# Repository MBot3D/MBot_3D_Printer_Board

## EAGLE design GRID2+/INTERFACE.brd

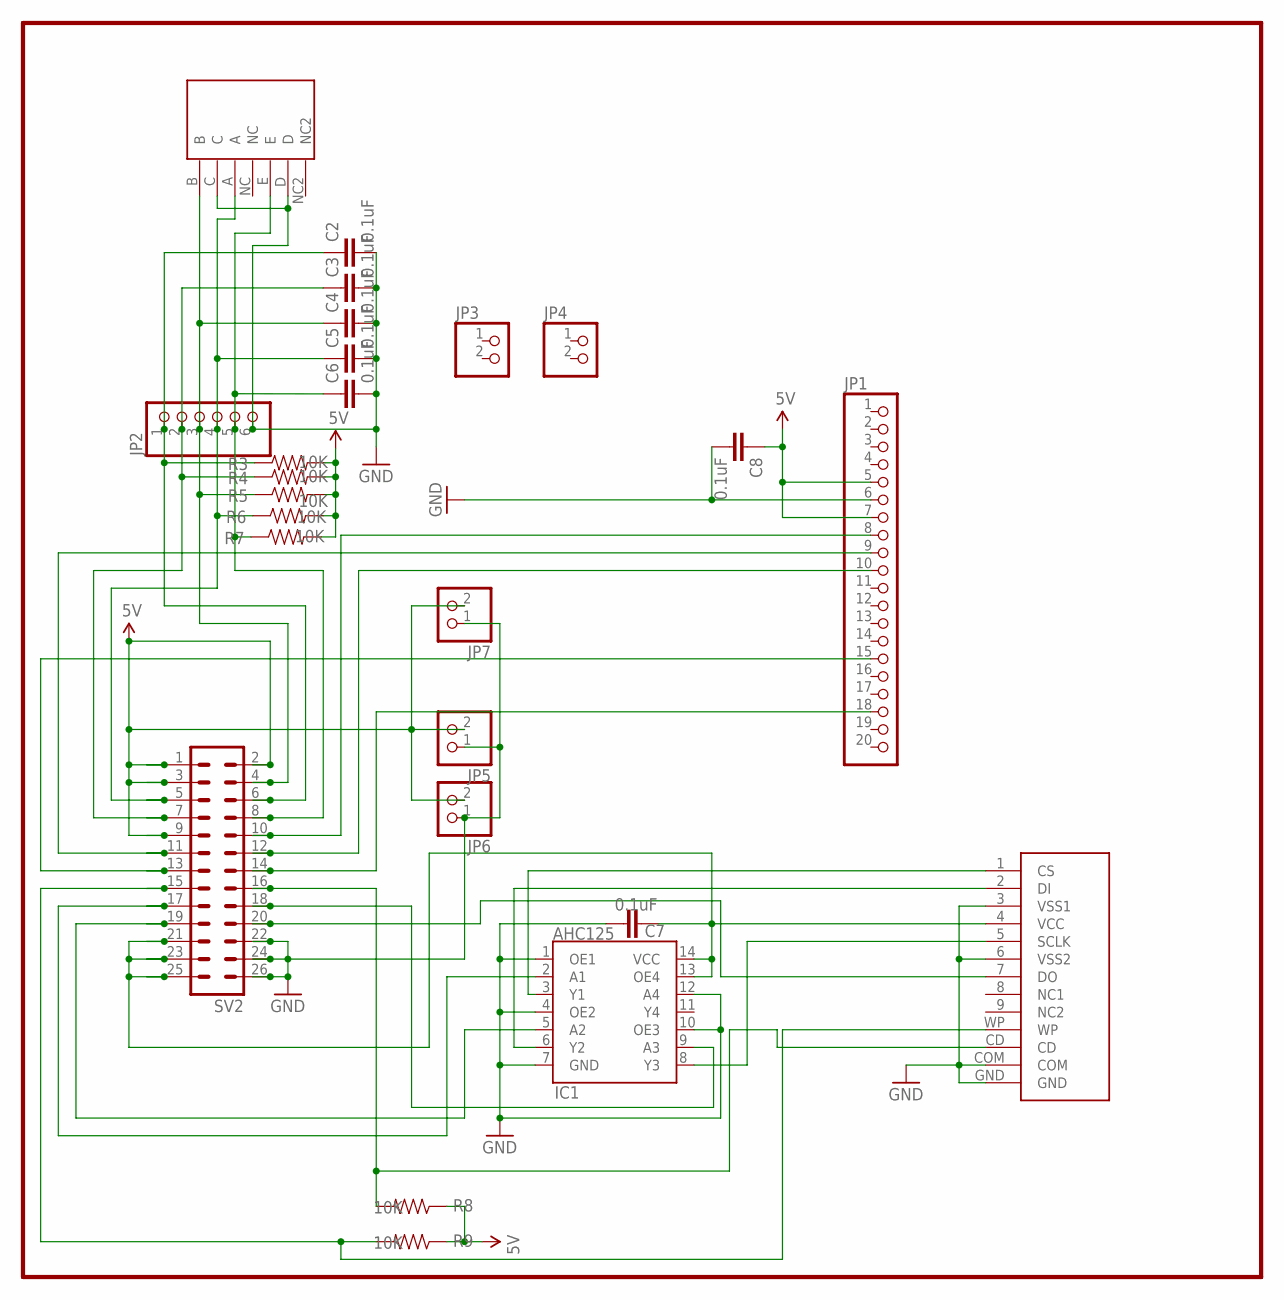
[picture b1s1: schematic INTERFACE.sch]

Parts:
C2, C3, C4, C5, C6, C7, C8: 0.1uF; 0805
IC1: AHC125; DIN14
JP1: PINHD-1X20; 1X20
JP2: PINHD-1X6; 1X06
JP3, JP4, JP5, JP6, JP7: PINHD-1X2; 1X02
Q2: SDCARD
R3, R4, R5, R6, R7, R8, R9: 10K; 0805
S2: DJFS; PIN5
SV2: ML26L

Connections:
5V: C8.1, JP1.5, JP1.7, JP5.2, JP6.2, JP7.2, R3.2, R4.2, R5.2, R6.2, R7.2, R8.1, R9.1, SV2.1, SV2.2, SV2.3, SV2.9
GND2: C2.2, C3.2, C4.2, C5.2, C6.2, C7.2, C8.2, IC1.1 (OE1), IC1.4 (OE2), IC1.7 (GND), IC1.10 (OE3), IC1.12 (A4), JP1.6, JP2.6, JP5.1, JP6.1, JP7.1, Q2.3 (VSS1), Q2.6 (VSS2), Q2.COM, Q2.GND, S2.C, S2.D, SV2.22, SV2.24, SV2.26
unnamed: IC1.3 (Y1), Q2.1 (CS)
unnamed: C2.1, JP2.1, R3.1, SV2.6
unnamed: IC1.2 (A1), SV2.17
unnamed: IC1.6 (Y2), Q2.2 (DI)
unnamed: Q2.CD, R8.2, SV2.16
unnamed: Q2.7 (DO), SV2.20
unnamed: JP1.15, SV2.13
unnamed: JP1.8, SV2.10
unnamed: JP1.10, SV2.12
unnamed: JP1.9, SV2.11
unnamed: JP1.18, SV2.14
unnamed: IC1.8 (Y3), Q2.5 (SCLK)
unnamed: C3.1, JP2.2, R4.1, SV2.7
unnamed: C4.1, JP2.3, R5.1, S2.B, SV2.4
unnamed: C5.1, JP2.4, R6.1, S2.A, SV2.5
unnamed: C6.1, JP2.5, R7.1, S2.E, SV2.8
unnamed: Q2.WP, R9.2, SV2.15
unnamed: IC1.5 (A2), SV2.19
unnamed: C7.1, IC1.13 (OE4), IC1.14 (VCC), Q2.4 (VCC), SV2.21, SV2.23, SV2.25
unnamed: IC1.9 (A3), SV2.18

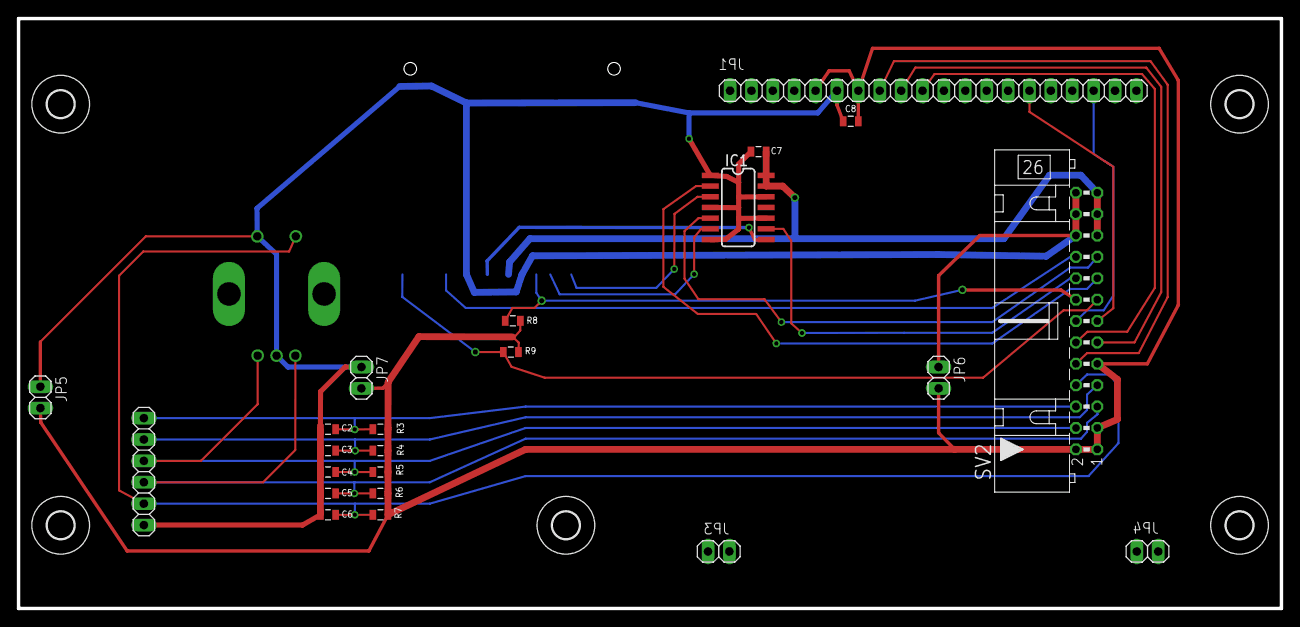
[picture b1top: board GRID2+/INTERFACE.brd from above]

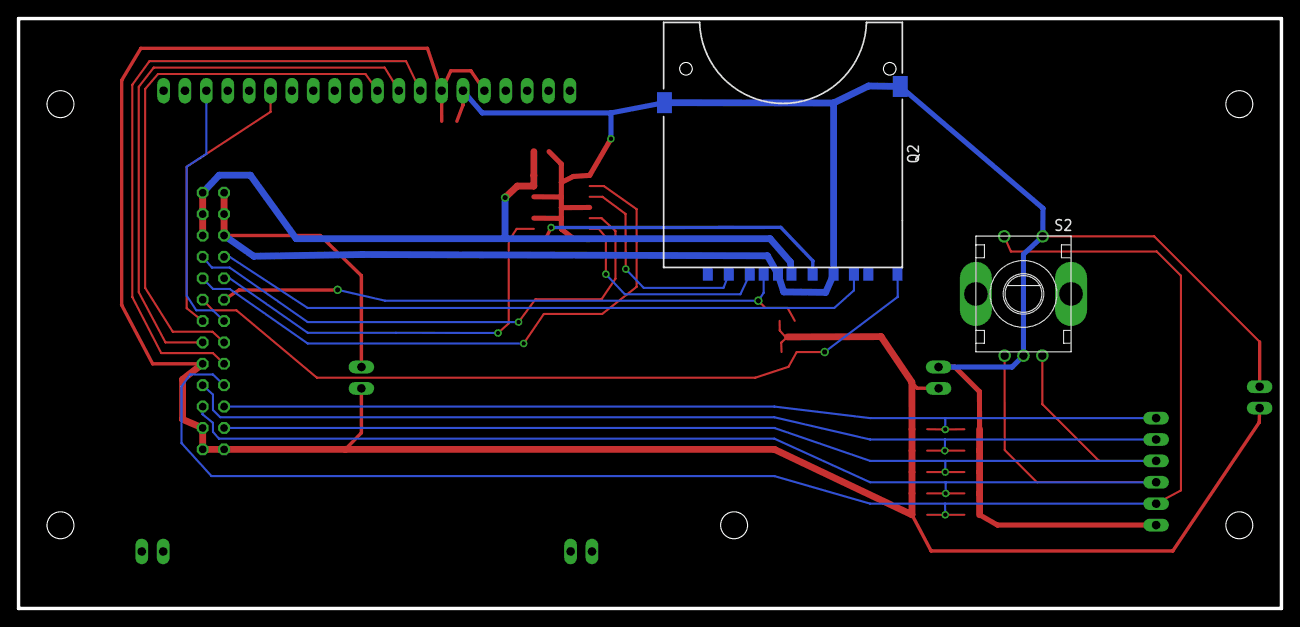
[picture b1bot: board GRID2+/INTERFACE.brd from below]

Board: 2 copper layers, 150.0 x 70.1 mm, 30 parts (2 on the bottom side), 22 nets.

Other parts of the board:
U$3, U$5, U$11, U$12, U$13: 3,2

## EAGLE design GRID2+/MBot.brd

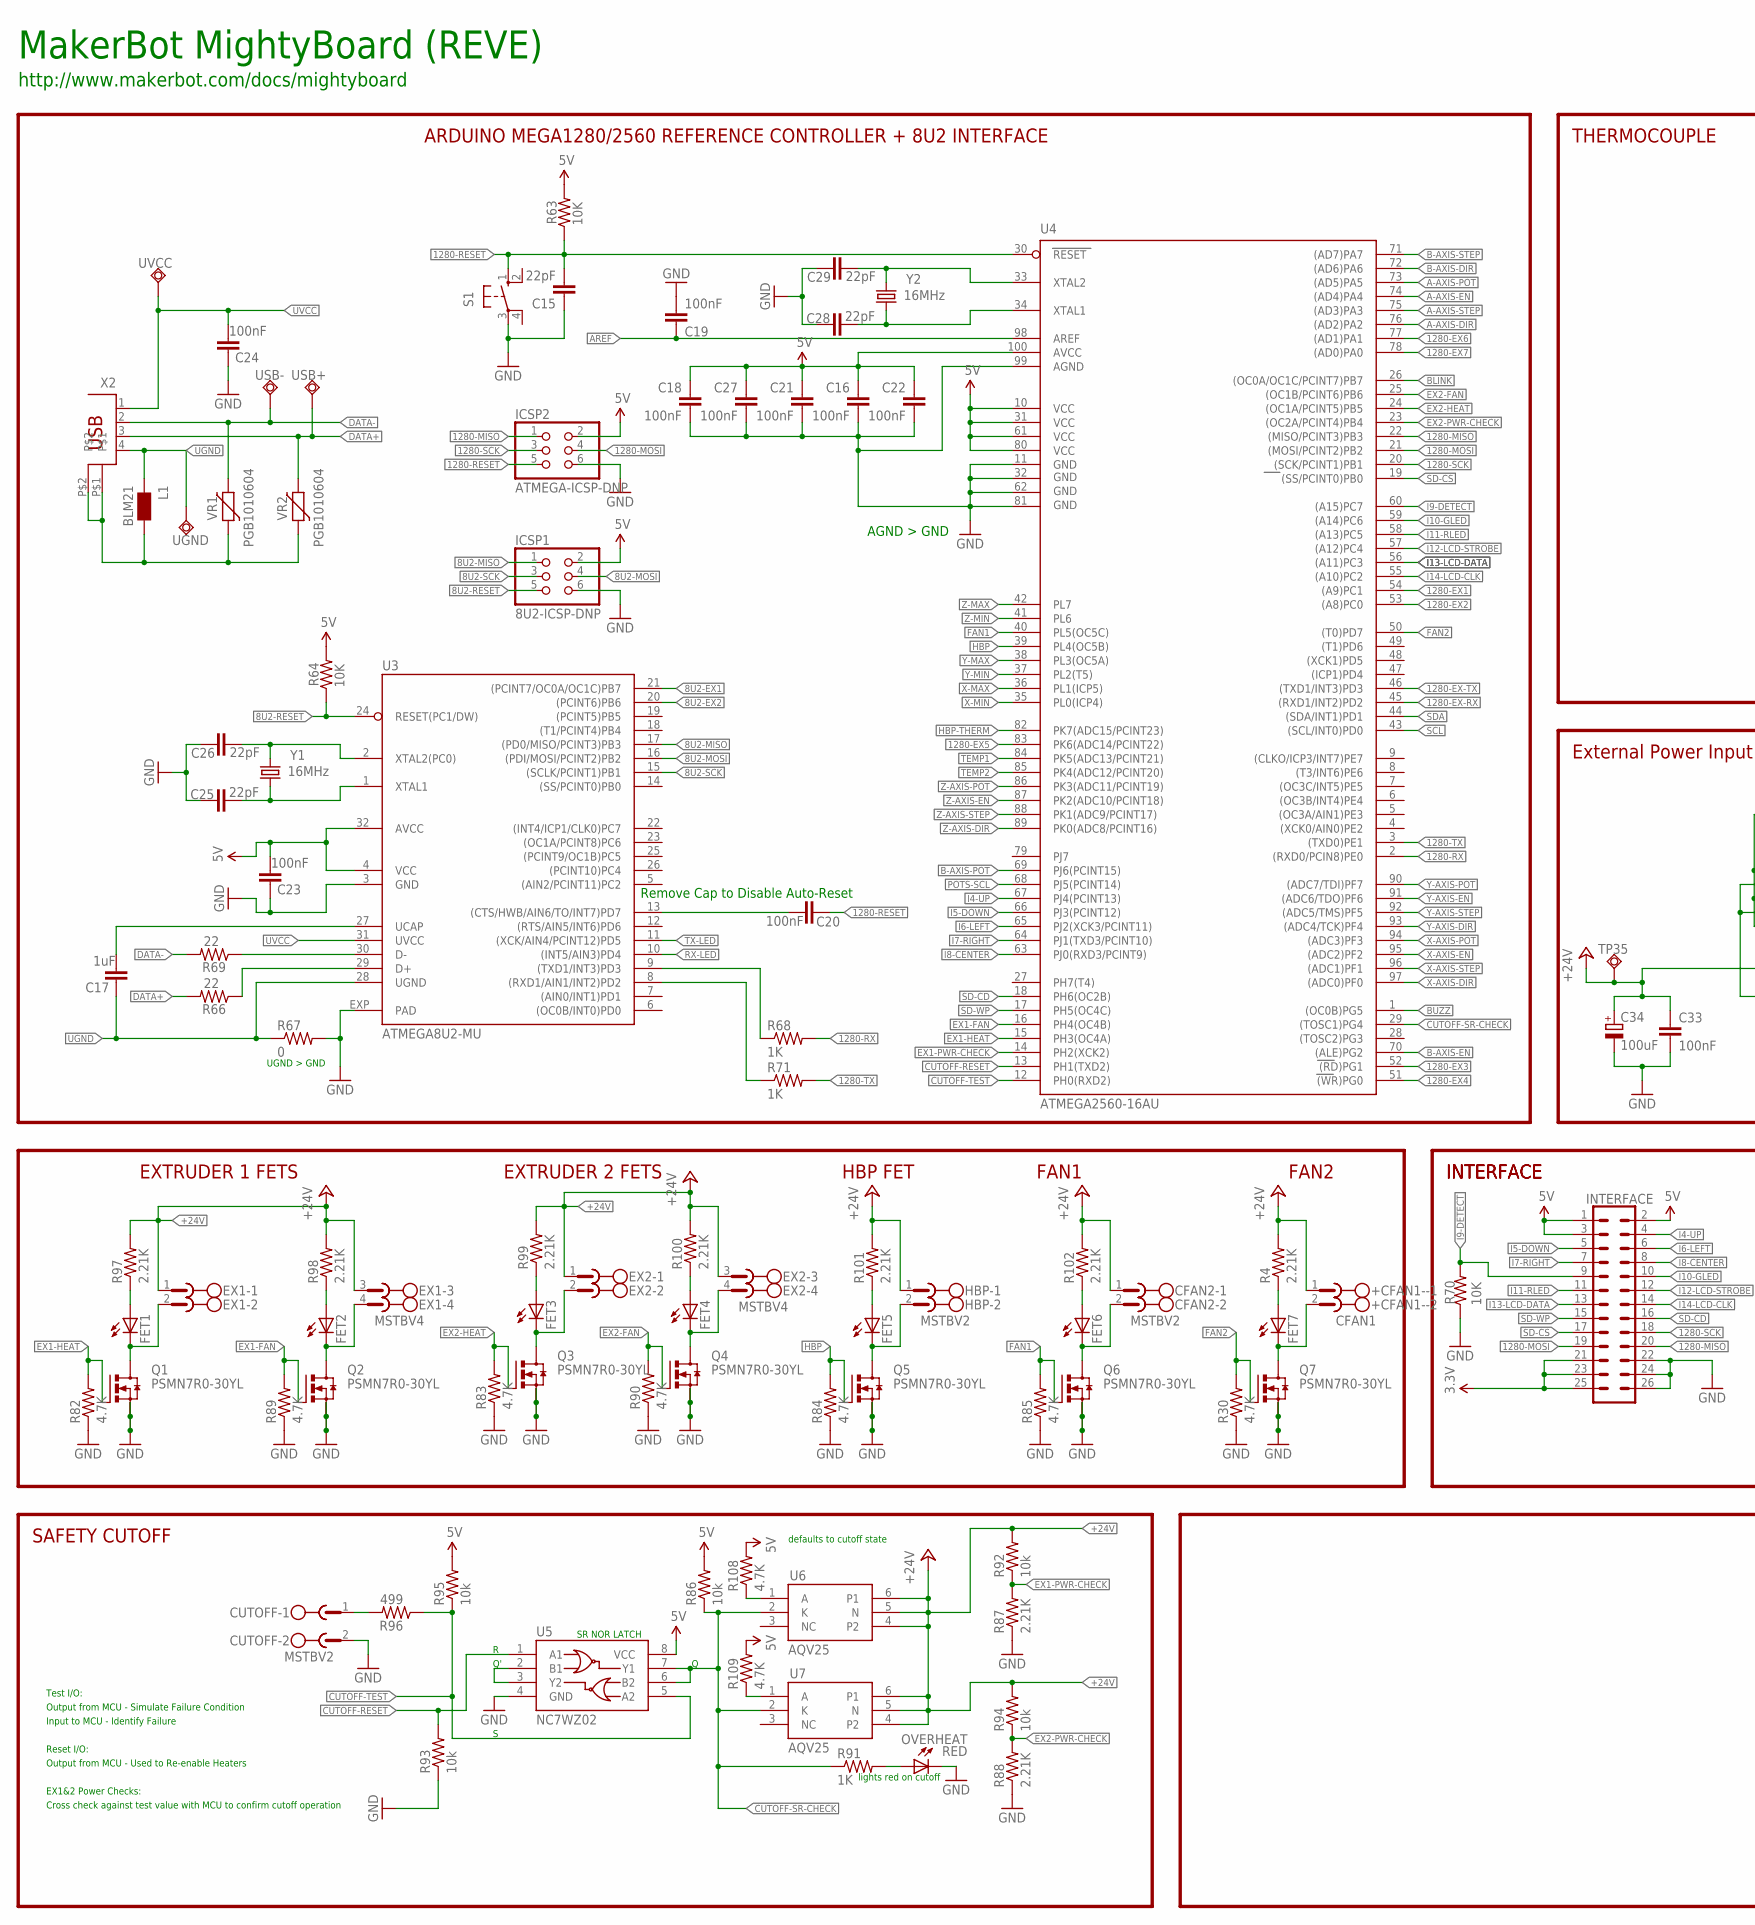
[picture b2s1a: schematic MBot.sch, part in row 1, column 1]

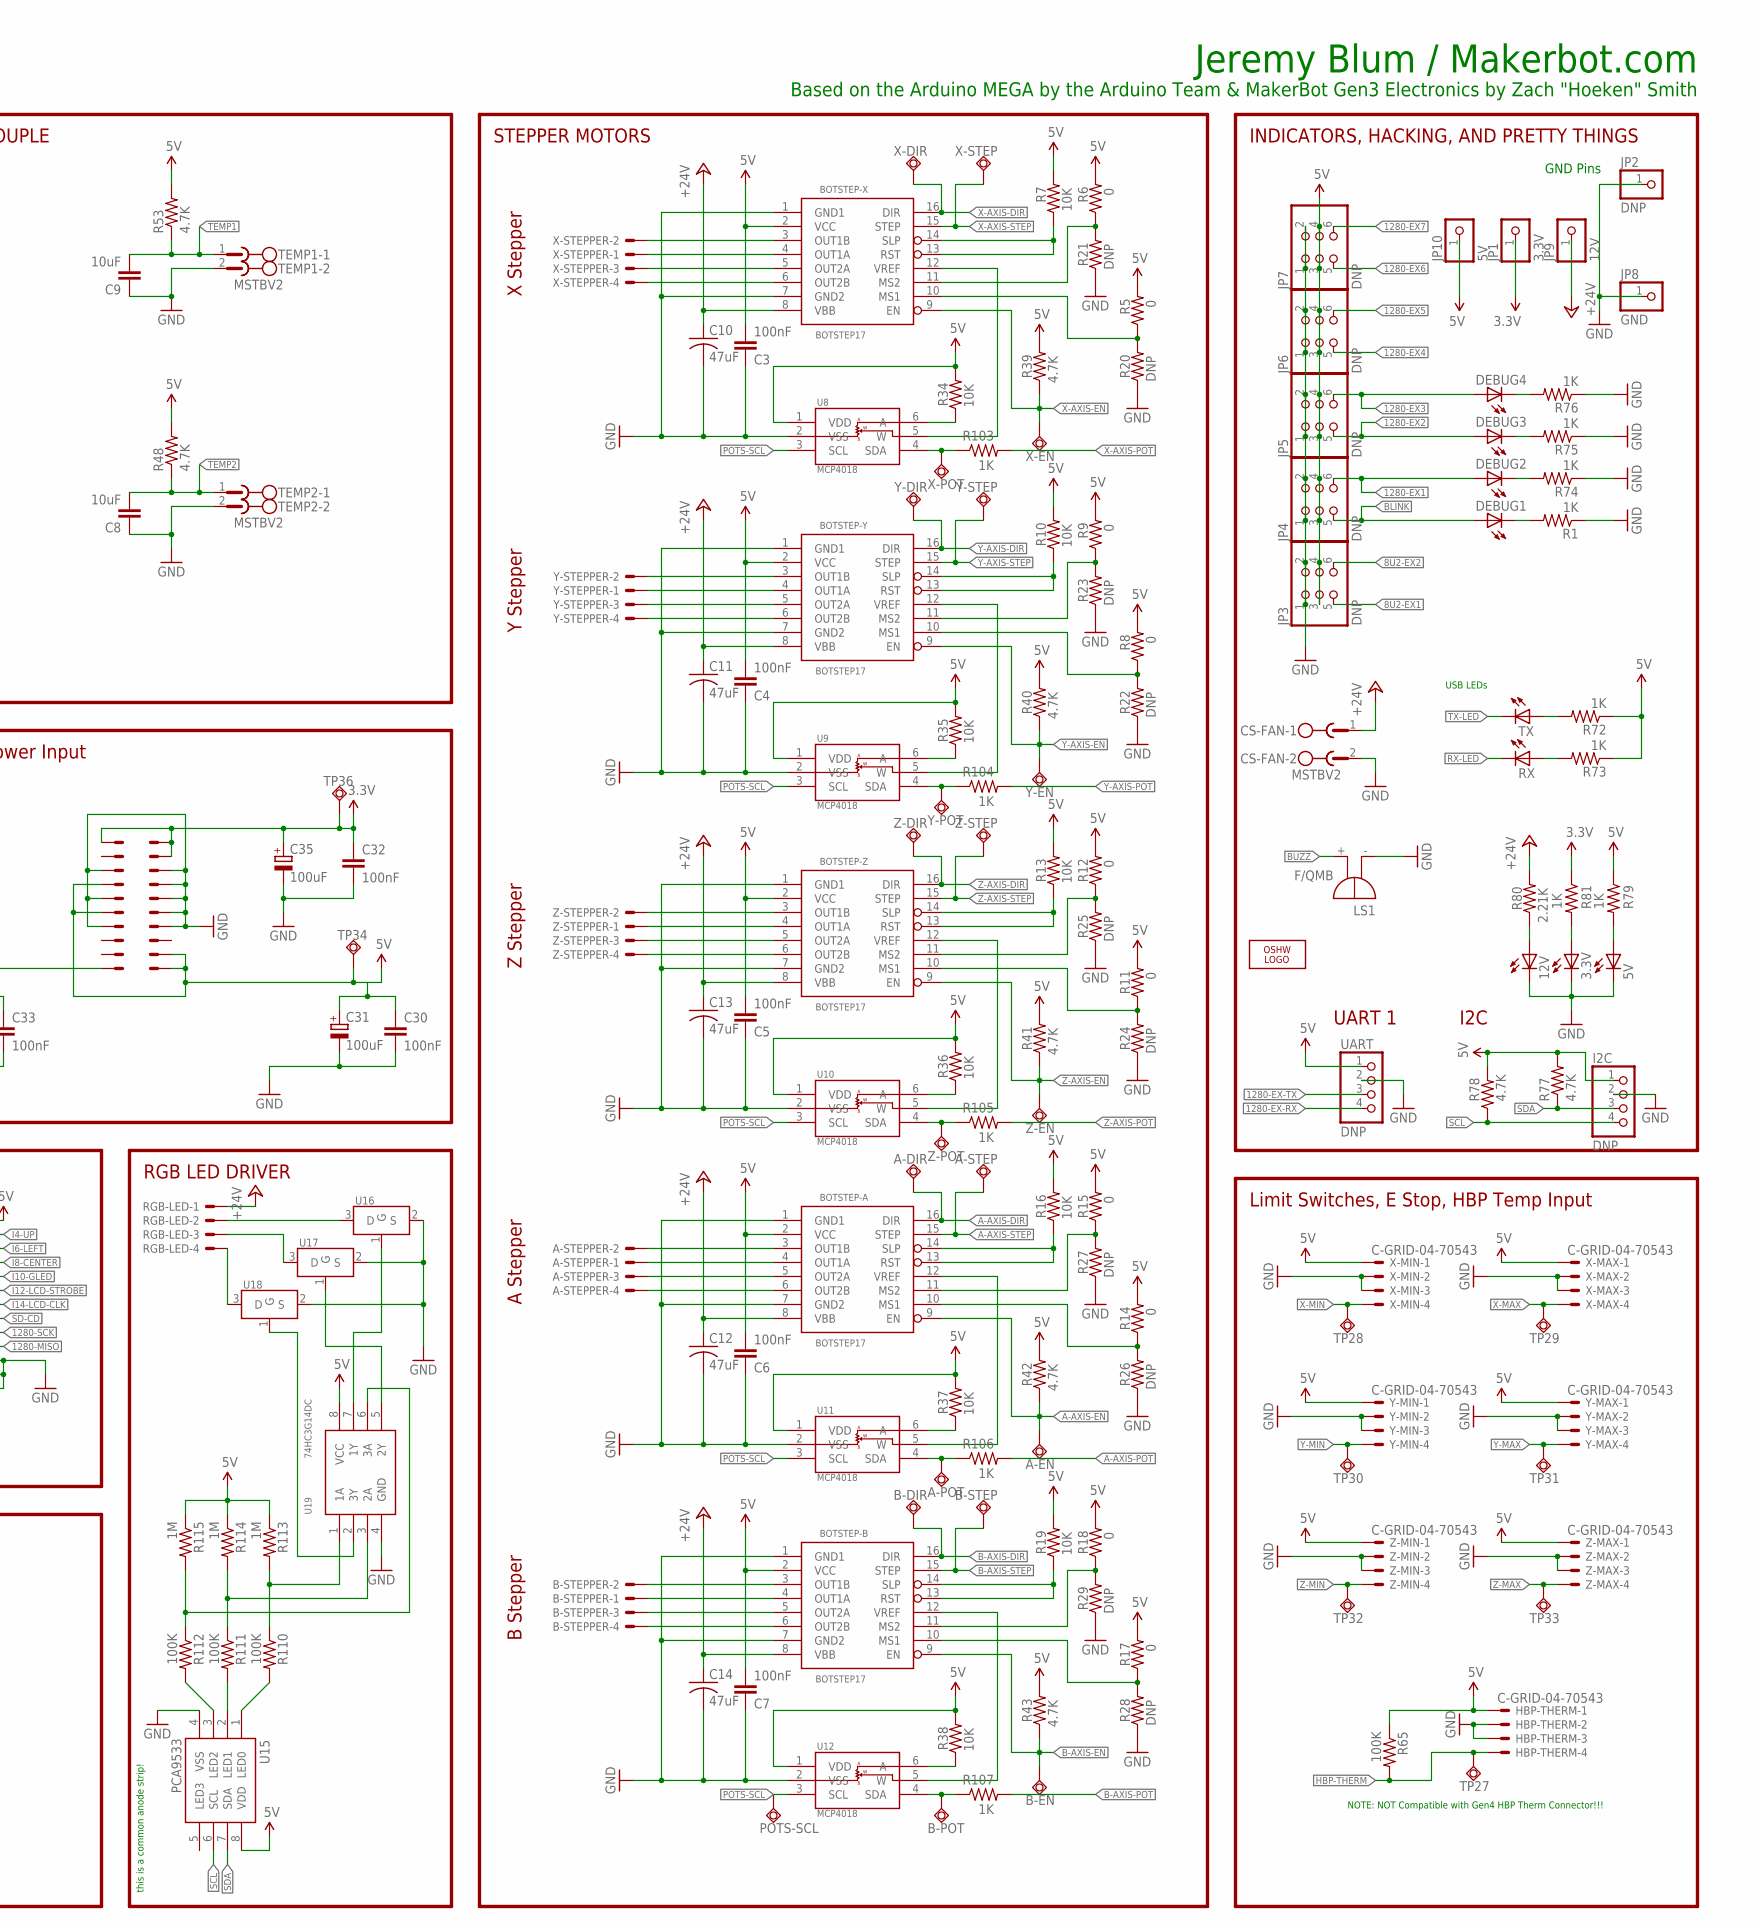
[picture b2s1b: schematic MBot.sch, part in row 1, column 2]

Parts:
3.3V, 5V, 12V: GREEN; LED-0805
+CFAN1-: CFAN1; MSTBV2
A-DIR: TPSQTP09R; TP09R
A-EN: TPSQTP09R; TP09R
A-POT: TPSQTP09R; TP09R
A-STEP: TPSQTP09R; TP09R
A-STEPPER: KK-156-4
B-DIR: TPSQTP09R; TP09R
B-EN: TPSQTP09R; TP09R
B-POT: TPSQTP09R; TP09R
B-STEP: TPSQTP09R; TP09R
B-STEPPER: KK-156-4
BOTSTEP-A: BOTSTEP17; BOTSTEP17-INV
BOTSTEP-B: BOTSTEP17; BOTSTEP17-INV
BOTSTEP-X: BOTSTEP17; BOTSTEP17-INV
BOTSTEP-Y: BOTSTEP17; BOTSTEP17-INV
BOTSTEP-Z: BOTSTEP17; BOTSTEP17-INV
C3, C4, C5, C6, C7, C16, C18, C19, C20, C21, C22, C23, C24, C27, C30, C32, C33: 100nF; 0805
C8, C9: 10uF; 0805
C10, C11, C12, C13, C14: 47uF; CAP2917
C15, C25, C26, C28, C29: 22pF; 0805
C17: 1uF; 0805
C31, C34, C35: 100uF; E3,5-8
CFAN2: MSTBV2
CS-FAN: MSTBV2
CUTOFF: MSTBV2
DEBUG1, DEBUG2, DEBUG3, DEBUG4: GREEN; LED-0805
EX1, EX2: MSTBV4
FET1, FET2, FET3, FET4, FET5, FET6, FET7: GREEN; LED-0805
HBP: MSTBV2
HBP-THERM: C-GRID-04-70543; 70543-04
I2C: DNP; 1X04
ICSP1: 8U2-ICSP-DNP; 2X03
ICSP2: ATMEGA-ICSP-DNP; 2X03
INTERFACE: ML26
JP1: 3.3V; 1X01
JP2: DNP; 1X01
JP3, JP4, JP5, JP6, JP7: DNP; 2X03
JP8: GND; 1X01
JP9: 12V; 1X01
JP10: 5V; 1X01
L1: BLM21; 0805
LOGO2: OSHW_LOGO_10MILX0200-NT; OSHW_10X200_NOTEXT
LS1: F/QMB
OVERHEAT: RED; LED-0805
POTS-SCL: TPSQTP09R; TP09R
Q1, Q2, Q3, Q4, Q5, Q6, Q7: PSMN7R0-30YL; SOT669
R1, R68, R71, R72, R73, R74, R75, R76, R79, R81, R91, R103, R104, R105, R106, R107: 1K; 0805
R4, R80, R87, R88, R97, R98, R99, R100, R101, R102: 2.21K; 0805
R5, R6, R8, R9, R11, R12, R14, R15, R17, R18, R67: 0; 0805
R7, R10, R13, R16, R19, R34, R35, R36, R37, R38, R63, R64, R70: 10K; 0805
R20, R21, R22, R23, R24, R25, R26, R27, R28, R29: DNP; 0805
R30, R39, R40, R41, R42, R43, R48, R53, R77, R78, R82, R83, R84, R85, R89, R90, R108, R109: 4.7K; 0805
R65, R110, R111, R112: 100K; 0805
R66, R69: 22; 0805
R86, R92, R93, R94, R95: 10k; 0805
R96: 499; 0805
R113, R114, R115: 1M; 0805
RGB-LED: C-GRID-04-70543; 70543-04
RX: GREEN; LED-0805
S1: 10-XX; B3F-10XX
TEMP1, TEMP2: MSTBV2; MPN MSTBV 2,5/2-GF-5.08
TP27, TP28, TP29, TP30, TP31, TP32, TP33, TP34, TP35, TP36: TPSQTP09R; TP09R
TX: GREEN; LED-0805
U3: ATMEGA8U2-MU; QFN32
U4: ATMEGA2560-16AU; TQFP100
U5: NC7WZ02; US8
U6, U7: AQV25; AQV25-DIPSM
U8, U9, U10, U11, U12: MCP4018; SC70-6L
U15: PCA9533; SO8
U16, U17, U18: FDV301N; SOT-23
U19: 74HC3G14DC; VSSOP8
UART: DNP; 1X04
UGND: TPSQTP09R; TP09R
USB+: TPSQTP09R; TP09R
USB-: TPSQTP09R; TP09R
UVCC: TPSQTP09R; TP09R
VR1, VR2: PGB1010604; CT/CN0603
X2: USBA; SMARTPRJ_PN61729
X3: 5569
X-DIR: TPSQTP09R; TP09R
X-EN: TPSQTP09R; TP09R
X-MAX: C-GRID-04-70543; 70543-04
X-MIN: C-GRID-04-70543; 70543-04
X-POT: TPSQTP09R; TP09R
X-STEP: TPSQTP09R; TP09R
X-STEPPER: KK-156-4
Y1, Y2: 16MHz; HC49/S
Y-DIR: TPSQTP09R; TP09R
Y-EN: TPSQTP09R; TP09R
Y-MAX: C-GRID-04-70543; 70543-04
Y-MIN: C-GRID-04-70543; 70543-04
Y-POT: TPSQTP09R; TP09R
Y-STEP: TPSQTP09R; TP09R
Y-STEPPER: KK-156-4
Z-DIR: TPSQTP09R; TP09R
Z-EN: TPSQTP09R; TP09R
Z-MAX: C-GRID-04-70543; 70543-04
Z-MIN: C-GRID-04-70543; 70543-04
Z-POT: TPSQTP09R; TP09R
Z-STEP: TPSQTP09R; TP09R
Z-STEPPER: KK-156-4

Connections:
3.3V: C32.1, C35.+, INTERFACE.21, INTERFACE.23, INTERFACE.25, JP1.1, R81.1, TP36.TP, X3.1, X3.2, X3.4
5V: BOTSTEP-A.2 (VCC), BOTSTEP-B.2 (VCC), BOTSTEP-X.2 (VCC), BOTSTEP-Y.2 (VCC), BOTSTEP-Z.2 (VCC), C3.2, C4.2, C5.2, C6.2, C7.2, C16.1, C18.1, C21.1, C22.1, C23.2, C27.1, C30.1, C31.+, HBP-THERM.1, I2C.1, ICSP1.2, ICSP2.2, INTERFACE.1, INTERFACE.2, INTERFACE.3, JP3.3, JP3.4, JP4.3, JP4.4, JP5.3, JP5.4, JP6.3, JP6.4, JP7.3, JP7.4, JP10.1, R5.2, R6.2, R7.2, R8.2, R9.2, R10.2, R11.2, R12.2, R13.2, R14.2, R15.2, R16.2, R17.2, R18.2, R19.2, R34.2, R35.2, R36.2, R37.2, R38.2, R39.2, R40.2, R41.2, R42.2, R43.2, R48.2, R53.2, R63.2, R64.2, R65.1, R72.1, R73.1, R77.2, R78.2, R79.1, R86.2, R95.2, R108.2, R109.2, R113.1, R114.1, R115.1, TP34.TP, U3.4 (VCC), U3.32 (AVCC), U4.10 (VCC), U4.31 (VCC1), U4.61 (VCC2), U4.80 (VCC3), U4.100 (AVCC), U5.8 (VCC), U8.1 (VDD), U9.1 (VDD), U10.1 (VDD), U11.1 (VDD), U12.1 (VDD), U15.8 (VDD), U19.8 (VCC), UART.1, X3.7, X3.11, X3.18, X3.20, X-MAX.1, X-MIN.1, Y-MAX.1, Y-MIN.1, Z-MAX.1, Z-MIN.1
8U2-EX1: JP3.5, U3.21 ((PCINT7/OC0A/OC1C)PB7)
8U2-EX2: JP3.6, U3.20 ((PCINT6)PB6)
8U2-MISO: ICSP1.1, U3.17 ((PD0/MISO/PCINT3)PB3)
8U2-MOSI: ICSP1.4, U3.16 ((PDI/MOSI/PCINT2)PB2)
8U2-RESET: ICSP1.5, R64.1, U3.24 (RESET(PC1/DW))
8U2-SCK: ICSP1.3, U3.15 ((SCLK/PCINT1)PB1)
1280-EX1: DEBUG2.A, JP4.6, U4.54 ((A9)PC1)
1280-EX2: DEBUG3.A, JP5.5, U4.53 ((A8)PC0)
1280-EX3: DEBUG4.A, JP5.6, U4.52 ((RD)PG1)
1280-EX4: JP6.5, U4.51 ((WR)PG0)
1280-EX5: JP6.6, U4.83 (PK6(ADC14/PCINT22))
1280-EX6: JP7.5, U4.77 ((AD1)PA1)
1280-EX7: JP7.6, U4.78 ((AD0)PA0)
1280-EX-RX: U4.45 ((RXD1/INT2)PD2), UART.4
1280-EX-TX: U4.46 ((TXD1/INT3)PD3), UART.3
1280-MISO: ICSP2.1, INTERFACE.20, U4.22 ((MISO/PCINT3)PB3)
1280-MOSI: ICSP2.4, INTERFACE.19, U4.21 ((MOSI/PCINT2)PB2)
1280-RESET: C15.2, C20.1, ICSP2.5, R63.1, S1.1 (S), U4.30 (RESET)
1280-RX: R68.2, U4.2 ((RXD0/PCIN8)PE0)
1280-SCK: ICSP2.3, INTERFACE.18, U4.20 ((SCK/PCINT1)PB1)
1280-TX: R71.2, U4.3 ((TXD0)PE1)
+24V: +CFAN1-.1, BOTSTEP-A.8 (VBB), BOTSTEP-B.8 (VBB), BOTSTEP-X.8 (VBB), BOTSTEP-Y.8 (VBB), BOTSTEP-Z.8 (VBB), C10.1, C11.1, C12.1, C13.1, C14.1, C33.1, C34.+, CFAN2.1, CS-FAN.1, EX1.1, EX1.3, EX2.1, EX2.3, HBP.1, JP9.1, R4.2, R80.2, R92.2, R94.2, R97.2, R98.2, R99.2, R100.2, R101.2, R102.2, RGB-LED.1, TP35.TP, U6.4 (P2), U6.5 (N), U6.6 (P1), U7.4 (P2), U7.5 (N), U7.6 (P1), X3.19
A-AXIS-DIR: A-DIR.TP, BOTSTEP-A.16 (DIR), U4.76 ((AD2)PA2)
A-AXIS-EN: A-EN.TP, BOTSTEP-A.9 (EN), R42.1, U4.74 ((AD4)PA4)
A-AXIS-POT: R106.2, U4.73 ((AD5)PA5)
A-AXIS-STEP: A-STEP.TP, BOTSTEP-A.15 (STEP), U4.75 ((AD3)PA3)
APWR1: EX1.4, FET2.C, Q2.MB (D)
AREF: C19.1, U4.98 (AREF)
B-AXIS-DIR: B-DIR.TP, BOTSTEP-B.16 (DIR), U4.72 ((AD6)PA6)
B-AXIS-EN: B-EN.TP, BOTSTEP-B.9 (EN), R43.1, U4.70 ((ALE)PG2)
B-AXIS-POT: R107.2, U4.69 (PJ6(PCINT15))
B-AXIS-STEP: B-STEP.TP, BOTSTEP-B.15 (STEP), U4.71 ((AD7)PA7)
BLINK: DEBUG1.A, JP4.5, U4.26 ((OC0A/OC1C/PCINT7)PB7)
BPWR: EX2.2, FET3.C, Q3.MB (D)
BPWR1: EX2.4, FET4.C, Q4.MB (D)
BUZZ: LS1.+ (-), U4.1 ((OC0B)PG5)
CPWR: FET5.C, HBP.2, Q5.MB (D)
CUTOFF-RESET: R93.2, U4.13 (PH1(TXD2)), U5.1 (A1)
CUTOFF-SR-CHECK: R86.1, R91.1, U4.29 ((TOSC1)PG4), U5.6 (B2), U5.7 (Y1), U6.2 (K), U7.2 (K)
CUTOFF-TEST: R95.1, R96.1, U4.12 (PH0(RXD2)), U5.5 (A2)
DATA+: R66.2, USB+.TP, VR2.2, X2.3
DATA-: R69.2, USB-.TP, VR1.2, X2.2
DPWR: CFAN2.2, FET6.C, Q6.MB (D)
DPWR1: +CFAN1-.2, FET7.C, Q7.MB (D)
DTR: C20.2, U3.13 ((CTS/HWB/AIN6/TO/INT7)PD7)
EX1-FAN: Q2.4 (G), R89.2, U4.16 (PH4(OC4B))
EX1-HEAT: Q1.4 (G), R82.2, U4.15 (PH3(OC4A))
EX1-PWR-CHECK: R87.2, R92.1, U4.14 (PH2(XCK2))
EX2-FAN: Q4.4 (G), R90.2, U4.25 ((OC1B/PCINT6)PB6)
EX2-HEAT: Q3.4 (G), R83.2, U4.24 ((OC1A/PCINT5)PB5)
EX2-PWR-CHECK: R88.2, R94.1, U4.23 ((OC2A/PCINT4)PB4)
FAN1: Q6.4 (G), R85.2, U4.40 (PL5(OC5C))
FAN2: Q7.4 (G), R30.2, U4.50 ((T0)PD7)
GND: 3.3V.C, 5V.C, 12V.C, BOTSTEP-A.1 (GND1), BOTSTEP-A.7 (GND2), BOTSTEP-B.1 (GND1), BOTSTEP-B.7 (GND2), BOTSTEP-X.1 (GND1), BOTSTEP-X.7 (GND2), BOTSTEP-Y.1 (GND1), BOTSTEP-Y.7 (GND2), BOTSTEP-Z.1 (GND1), BOTSTEP-Z.7 (GND2), C3.1, C4.1, C5.1, C6.1, C7.1, C8.1, C9.1, C10.2, C11.2, C12.2, C13.2, C14.2, C15.1, C16.2, C18.2, C19.2, C21.2, C22.2, C23.1, C24.1, C25.1, C26.1, C27.2, C28.1, C29.1, C30.2, C31.-, C32.2, C33.2, C34.-, C35.-, CS-FAN.2, CUTOFF.2, HBP-THERM.2, HBP-THERM.3, I2C.2, ICSP1.6, ICSP2.6, INTERFACE.22, INTERFACE.24, INTERFACE.26, JP2.1, JP3.1, JP3.2, JP4.1, JP4.2, JP5.1, JP5.2, JP6.1, JP6.2, JP7.1, JP7.2, JP8.1, LS1.- (+), OVERHEAT.C, Q1.1 (S), Q1.2 (S), Q1.3 (S), Q2.1 (S), Q2.2 (S), Q2.3 (S), Q3.1 (S), Q3.2 (S), Q3.3 (S), Q4.1 (S), Q4.2 (S), Q4.3 (S), Q5.1 (S), Q5.2 (S), Q5.3 (S), Q6.1 (S), Q6.2 (S), Q6.3 (S), Q7.1 (S), Q7.2 (S), Q7.3 (S), R1.1, R20.1, R21.1, R22.1, R23.1, R24.1, R25.1, R26.1, R27.1, R28.1, R29.1, R30.1, R67.2, R70.1, R74.1, R75.1, R76.1, R82.1, R83.1, R84.1, R85.1, R87.1, R88.1, R89.1, R90.1, R93.1, S1.3, TEMP1.2, TEMP2.2, U3.3 (GND), U3.EXP (PAD), U4.11 (GND), U4.32 (GND1), U4.62 (GND2), U4.81 (GND3), U4.99 (AGND), U5.4 (GND), U8.2 (VSS), U9.2 (VSS), U10.2 (VSS), U11.2 (VSS), U12.2 (VSS), U15.4 (VSS), U16.2 (S), U17.2 (S), U18.2 (S), U19.4 (GND), UART.2, X3.5, X3.6, X3.8, X3.9, X3.10, X3.12, X3.13, X3.14, X-MAX.2, X-MAX.3, X-MIN.2, X-MIN.3, Y-MAX.2, Y-MAX.3, Y-MIN.2, Y-MIN.3, Z-MAX.2, Z-MAX.3, Z-MIN.2, Z-MIN.3
HBP: Q5.4 (G), R84.2, U4.39 (PL4(OC5B))
HBP-THERM: HBP-THERM.4, R65.2, TP27.TP, U4.82 (PK7(ADC15/PCINT23))
I4-UP: INTERFACE.4, U4.67 (PJ4(PCINT13))
I5-DOWN: INTERFACE.5, U4.66 (PJ3(PCINT12))
I6-LEFT: INTERFACE.6, U4.65 (PJ2(XCK3/PCINT11))
I7-RIGHT: INTERFACE.7, U4.64 (PJ1(TXD3/PCINT10))
I8-CENTER: INTERFACE.8, U4.63 (PJ0(RXD3/PCINT9))
I9-DETECT: INTERFACE.9, R70.2, U4.60 ((A15)PC7)
I10-GLED: INTERFACE.10, U4.59 ((A14)PC6)
I11-RLED: INTERFACE.11, U4.58 ((A13)PC5)
I12-LCD-STROBE: INTERFACE.12, U4.57 ((A12)PC4)
I13-LCD-DATA: INTERFACE.13, U4.56 ((A11)PC3)
I14-LCD-CLK: INTERFACE.14, U4.55 ((A10)PC2)
M8RXD: R68.1, U3.9 ((TXD1/INT3)PD3)
M8TXD: R71.1, U3.8 ((RXD1/AIN1/INT2)PD2)
unnamed: 3.3V.A, R81.2
unnamed: C28.2, U4.34 (XTAL1), Y2.1
unnamed: 5V.A, R79.2
unnamed: DEBUG4.C, R76.2
unnamed: DEBUG1.C, R1.2
unnamed: FET2.A, R98.1
unnamed: FET4.A, R100.1
unnamed: 12V.A, R80.1
unnamed: FET6.A, R102.1
unnamed: C29.2, U4.33 (XTAL2), Y2.2
unnamed: DEBUG2.C, R74.2
unnamed: DEBUG3.C, R75.2
unnamed: FET5.A, R101.1
unnamed: BOTSTEP-X.10 (MS1), R5.1, R20.2
unnamed: FET7.A, R4.1
unnamed: CUTOFF.1, R96.2
unnamed: BOTSTEP-X.13 (RST), BOTSTEP-X.14 (SLP), R7.1
unnamed: FET1.A, R97.1
unnamed: FET3.A, R99.1
unnamed: BOTSTEP-X.12 (VREF), U8.5 (W)
unnamed: R34.1, U8.6 (A)
unnamed: BOTSTEP-X.11 (MS2), R6.1, R21.2
unnamed: BOTSTEP-Y.13 (RST), BOTSTEP-Y.14 (SLP), R10.1
unnamed: BOTSTEP-X.3 (OUT1B), X-STEPPER.2
unnamed: BOTSTEP-X.4 (OUT1A), X-STEPPER.1
unnamed: BOTSTEP-X.5 (OUT2A), X-STEPPER.3
unnamed: BOTSTEP-X.6 (OUT2B), X-STEPPER.4
unnamed: OVERHEAT.A, R91.2
unnamed: BOTSTEP-Y.12 (VREF), U9.5 (W)
unnamed: R35.1, U9.6 (A)
unnamed: BOTSTEP-Y.11 (MS2), R9.1, R23.2
unnamed: BOTSTEP-Y.3 (OUT1B), Y-STEPPER.2
unnamed: BOTSTEP-Y.4 (OUT1A), Y-STEPPER.1
unnamed: BOTSTEP-Y.5 (OUT2A), Y-STEPPER.3
unnamed: BOTSTEP-Y.6 (OUT2B), Y-STEPPER.4
unnamed: BOTSTEP-Y.10 (MS1), R8.1, R22.2
unnamed: BOTSTEP-Z.13 (RST), BOTSTEP-Z.14 (SLP), R13.1
unnamed: BOTSTEP-Z.12 (VREF), U10.5 (W)
unnamed: R36.1, U10.6 (A)
unnamed: BOTSTEP-Z.11 (MS2), R12.1, R25.2
unnamed: BOTSTEP-Z.3 (OUT1B), Z-STEPPER.2
unnamed: BOTSTEP-Z.4 (OUT1A), Z-STEPPER.1
unnamed: BOTSTEP-Z.5 (OUT2A), Z-STEPPER.3
unnamed: BOTSTEP-Z.6 (OUT2B), Z-STEPPER.4
unnamed: BOTSTEP-Z.10 (MS1), R11.1, R24.2
unnamed: BOTSTEP-A.13 (RST), BOTSTEP-A.14 (SLP), R16.1
unnamed: BOTSTEP-A.12 (VREF), U11.5 (W)
unnamed: R37.1, U11.6 (A)
unnamed: BOTSTEP-A.11 (MS2), R15.1, R27.2
unnamed: A-STEPPER.2, BOTSTEP-A.3 (OUT1B)
unnamed: A-STEPPER.1, BOTSTEP-A.4 (OUT1A)
unnamed: A-STEPPER.3, BOTSTEP-A.5 (OUT2A)
unnamed: A-STEPPER.4, BOTSTEP-A.6 (OUT2B)
unnamed: BOTSTEP-A.10 (MS1), R14.1, R26.2
unnamed: BOTSTEP-B.13 (RST), BOTSTEP-B.14 (SLP), R19.1
unnamed: BOTSTEP-B.12 (VREF), U12.5 (W)
unnamed: R38.1, U12.6 (A)
unnamed: BOTSTEP-B.11 (MS2), R18.1, R29.2
unnamed: B-STEPPER.2, BOTSTEP-B.3 (OUT1B)
unnamed: B-STEPPER.1, BOTSTEP-B.4 (OUT1A)
unnamed: B-STEPPER.3, BOTSTEP-B.5 (OUT2A)
unnamed: B-STEPPER.4, BOTSTEP-B.6 (OUT2B)
unnamed: BOTSTEP-B.10 (MS1), R17.1, R28.2
unnamed: R112.2, U15.3 (LED2)
unnamed: R111.2, U15.2 (LED1)
unnamed: R110.2, U15.1 (LED0)
unnamed: U5.2 (B1), U5.3 (Y2)
unnamed: R73.2, RX.A
unnamed: R72.2, TX.A
unnamed: C25.2, U3.1 (XTAL1), Y1.1
unnamed: C26.2, U3.2 (XTAL2(PC0)), Y1.2
unnamed: R110.1, R113.2, U19.1 (1A)
unnamed: R103.1, U8.4 (SDA), X-POT.TP
unnamed: R104.1, U9.4 (SDA), Y-POT.TP
unnamed: R105.1, U10.4 (SDA), Z-POT.TP
unnamed: A-POT.TP, R106.1, U11.4 (SDA)
unnamed: B-POT.TP, R107.1, U12.4 (SDA)
unnamed: R109.1, U7.1 (A)
unnamed: R108.1, U6.1 (A)
unnamed: U17.1 (G), U19.5 (2Y)
unnamed: U16.1 (G), U19.7 (1Y)
unnamed: R112.1, R115.2, U19.6 (3A)
unnamed: RGB-LED.4, U18.3 (D)
unnamed: RGB-LED.3, U17.3 (D)
unnamed: RGB-LED.2, U16.3 (D)
unnamed: R111.1, R114.2, U19.3 (2A)
unnamed: U18.1 (G), U19.2 (3Y)
unnamed: EX1.2, FET1.C, Q1.MB (D)
POTS-SCL: POTS-SCL.TP, U4.68 (PJ5(PCINT14)), U8.3 (SCL), U9.3 (SCL), U10.3 (SCL), U11.3 (SCL), U12.3 (SCL)
RD+: R66.1, U3.29 (D+)
RD-: R69.1, U3.30 (D-)
RX-LED: RX.C, U3.10 ((INT5/AIN3)PD4)
SCL: I2C.4, R78.1, U4.43 ((SCL/INT0)PD0), U15.6 (SCL)
SD-CD: INTERFACE.16, U4.18 (PH6(OC2B))
SD-CS: INTERFACE.17, U4.19 ((SS/PCINT0)PB0)
SD-WP: INTERFACE.15, U4.17 (PH5(OC4C))
SDA: I2C.3, R77.1, U4.44 ((SDA/INT1)PD1), U15.7 (SDA)
TEMP1: C9.2, R53.1, TEMP1.1, U4.84 (PK5(ADC13/PCINT21))
TEMP2: C8.2, R48.1, TEMP2.1, U4.85 (PK4(ADC12/PCINT20))
TX-LED: TX.C, U3.11 ((XCK/AIN4/PCINT12)PD5)
UGND: C17.1, L1.1, R67.1, U3.28 (UGND), UGND.TP, X2.4
USHIELD: L1.2, VR1.1, VR2.1, X2.P$1, X2.P$2
UVCC: C24.2, U3.31 (UVCC), UVCC.TP, X2.1
VUCAP: C17.2, U3.27 (UCAP)
X-AXIS-DIR: BOTSTEP-X.16 (DIR), U4.97 ((ADC0)PF0), X-DIR.TP
X-AXIS-EN: BOTSTEP-X.9 (EN), R39.1, U4.95 ((ADC2)PF2), X-EN.TP
X-AXIS-POT: R103.2, U4.94 ((ADC3)PF3)
X-AXIS-STEP: BOTSTEP-X.15 (STEP), U4.96 ((ADC1)PF1), X-STEP.TP
X-MAX: TP29.TP, U4.36 (PL1(ICP5)), X-MAX.4
X-MIN: TP28.TP, U4.35 (PL0(ICP4)), X-MIN.4
Y-AXIS-DIR: BOTSTEP-Y.16 (DIR), U4.93 ((ADC4/TCK)PF4), Y-DIR.TP
Y-AXIS-EN: BOTSTEP-Y.9 (EN), R40.1, U4.91 ((ADC6/TDO)PF6), Y-EN.TP
Y-AXIS-POT: R104.2, U4.90 ((ADC7/TDI)PF7)
Y-AXIS-STEP: BOTSTEP-Y.15 (STEP), U4.92 ((ADC5/TMS)PF5), Y-STEP.TP
Y-MAX: TP31.TP, U4.38 (PL3(OC5A)), Y-MAX.4
Y-MIN: TP30.TP, U4.37 (PL2(T5)), Y-MIN.4
Z-AXIS-DIR: BOTSTEP-Z.16 (DIR), U4.89 (PK0(ADC8/PCINT16)), Z-DIR.TP
Z-AXIS-EN: BOTSTEP-Z.9 (EN), R41.1, U4.87 (PK2(ADC10/PCINT18)), Z-EN.TP
Z-AXIS-POT: R105.2, U4.86 (PK3(ADC11/PCINT19))
Z-AXIS-STEP: BOTSTEP-Z.15 (STEP), U4.88 (PK1(ADC9/PCINT17)), Z-STEP.TP
Z-MAX: TP33.TP, U4.42 (PL7), Z-MAX.4
Z-MIN: TP32.TP, U4.41 (PL6), Z-MIN.4

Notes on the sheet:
External Power Input
X Stepper
MakerBot MightyBoard (REVE)
http://www.makerbot.com/docs/mightyboard
Jeremy Blum / Makerbot.com
Based on the Arduino MEGA by the Arduino Team & MakerBot Gen3 Electronics by Zach "Hoeken" Smith
Limit Switches, E Stop, HBP Temp Input
INTERFACE
ARDUINO MEGA1280/2560 REFERENCE CONTROLLER + 8U2 INTERFACE
EXTRUDER 2 FETS
EXTRUDER 1 FETS
INDICATORS, HACKING, AND PRETTY THINGS
THERMOCOUPLE
I2C
GND Pins
STEPPER MOTORS
UGND > GND
AGND > GND
Remove Cap to Disable Auto-Reset
HBP FET
RGB LED DRIVER
SAFETY CUTOFF
defaults to cutoff state
lights red on cutoff
Test I/O:
Output from MCU - Simulate Failure Condition
Input to MCU - Identify Failure
Reset I/O:
Output from MCU - Used to Re-enable Heaters
EX1&2 Power Checks:
Cross check against test value with MCU to confirm cutoff operation
Y Stepper
Z Stepper
A Stepper
B Stepper
UART 1
FAN1
this is a common anode strip!
USB LEDs
SR NOR LATCH

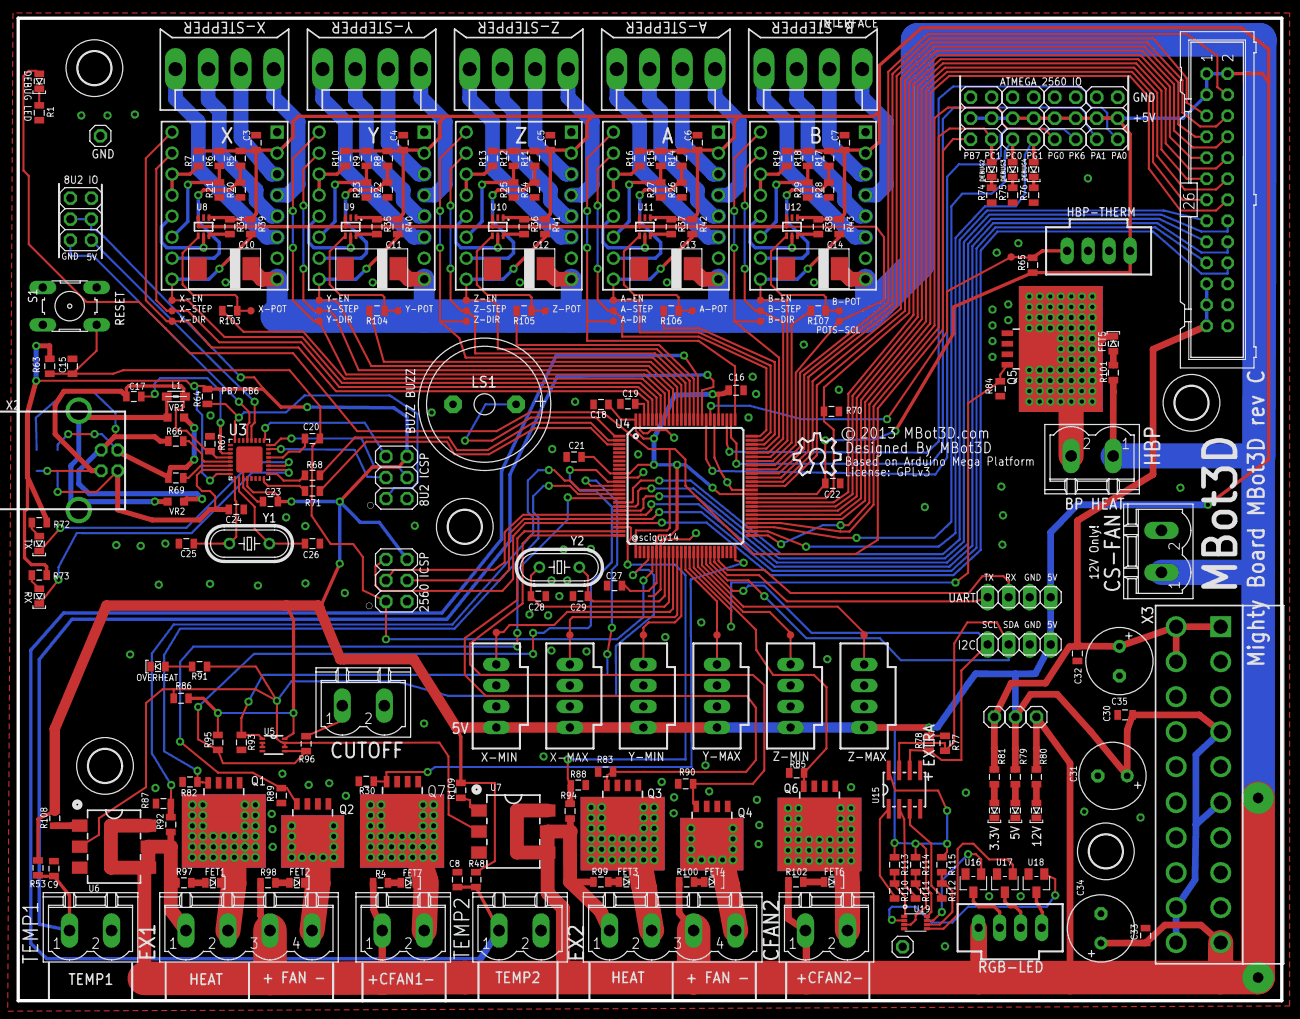
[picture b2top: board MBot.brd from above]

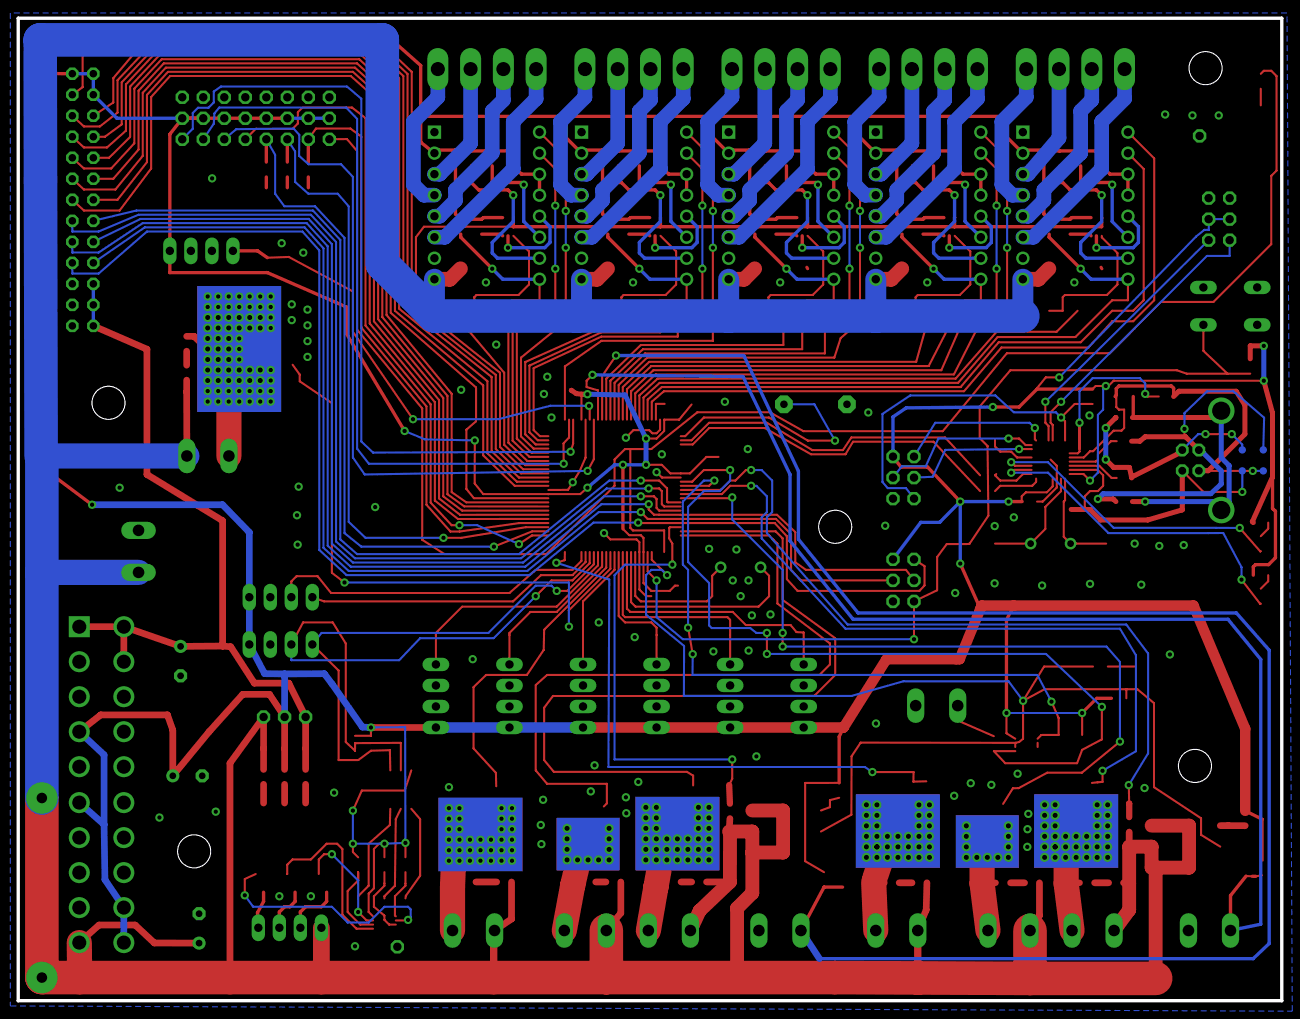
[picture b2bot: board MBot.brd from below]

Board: 2 copper layers, 152.7 x 118.7 mm, 257 parts (4 on the bottom side), 193 nets.

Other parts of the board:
$$$$$$U$1: 4,0HOLE-3,0KEEPOUT
$$U$1, $$U$7, $$U$8: 4,0HOLE-3,0KEEPOUT
U$1: 4,0HOLE-3,0KEEPOUT

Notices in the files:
GRID2+/MBot.brd:
License: GPLv3
parts and their libraries:
SparkFun2: Licensing: CC v3.0 Share-Alike You are welcome to use this library for commercial purposes.
